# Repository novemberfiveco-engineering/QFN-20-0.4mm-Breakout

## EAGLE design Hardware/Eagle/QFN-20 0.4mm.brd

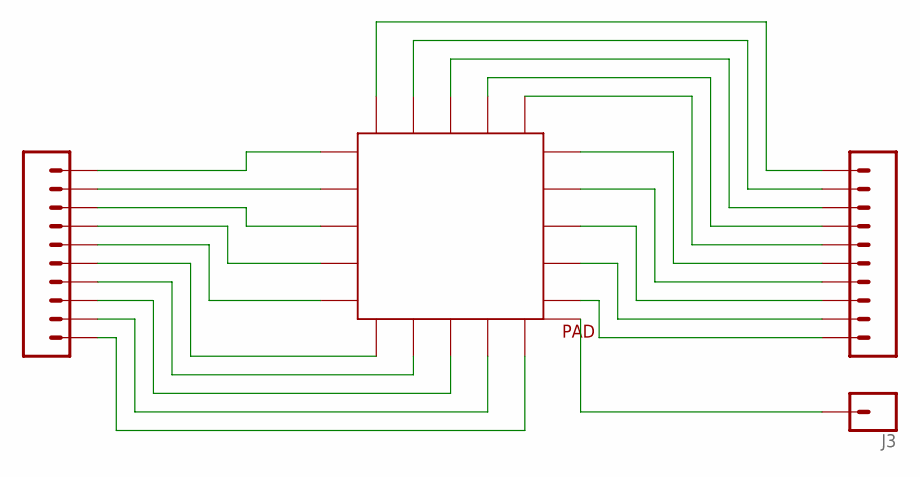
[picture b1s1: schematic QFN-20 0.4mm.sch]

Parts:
GND: QFN-20_0,4MM; QFN20_0,4MM
J1, J2: CONN_10"; 1X10
J3: CONN_01; 1X01

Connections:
unnamed: GND.1 (PIN1), J1.1
unnamed: GND.2 (PIN2), J1.2
unnamed: GND.3 (PIN3), J1.3
unnamed: GND.4 (PIN4), J1.4
unnamed: GND.5 (PIN5), J1.5
unnamed: GND.6 (PIN6), J1.6
unnamed: GND.7 (PIN7), J1.7
unnamed: GND.8 (PIN8), J1.8
unnamed: GND.9 (PIN9), J1.9
unnamed: GND.10 (PIN10), J1.10
unnamed: GND.0 (PAD), J3.1
unnamed: GND.11 (PIN11), J2.10
unnamed: GND.12 (PIN12), J2.9
unnamed: GND.13 (PIN13), J2.8
unnamed: GND.14 (PIN14), J2.7
unnamed: GND.15 (PIN15), J2.6
unnamed: GND.16 (PIN16), J2.5
unnamed: GND.17 (PIN17), J2.4
unnamed: GND.18 (PIN18), J2.3
unnamed: GND.19 (PIN19), J2.2
unnamed: GND.20 (PIN20), J2.1

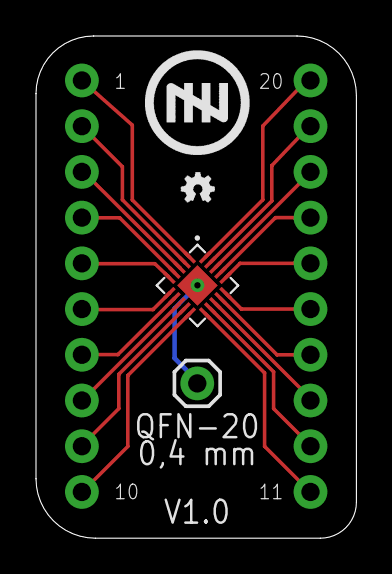
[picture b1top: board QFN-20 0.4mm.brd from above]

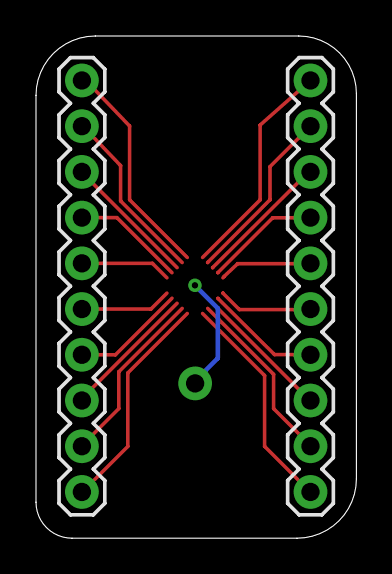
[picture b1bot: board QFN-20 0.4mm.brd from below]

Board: 2 copper layers, 17.8 x 27.9 mm, 6 parts (3 on the bottom side), 21 nets.

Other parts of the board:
U$2: LOGO-NOVEMERFIVE-7SCALE
U$3: LOGO-OSHWA

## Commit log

2017-05-15 Added project library

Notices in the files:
parts and their libraries:
SparkFun-Connectors: Licensing: Creative Commons ShareAlike 4.0 International - https://creativecommons.org/licenses/by-sa/4.0
